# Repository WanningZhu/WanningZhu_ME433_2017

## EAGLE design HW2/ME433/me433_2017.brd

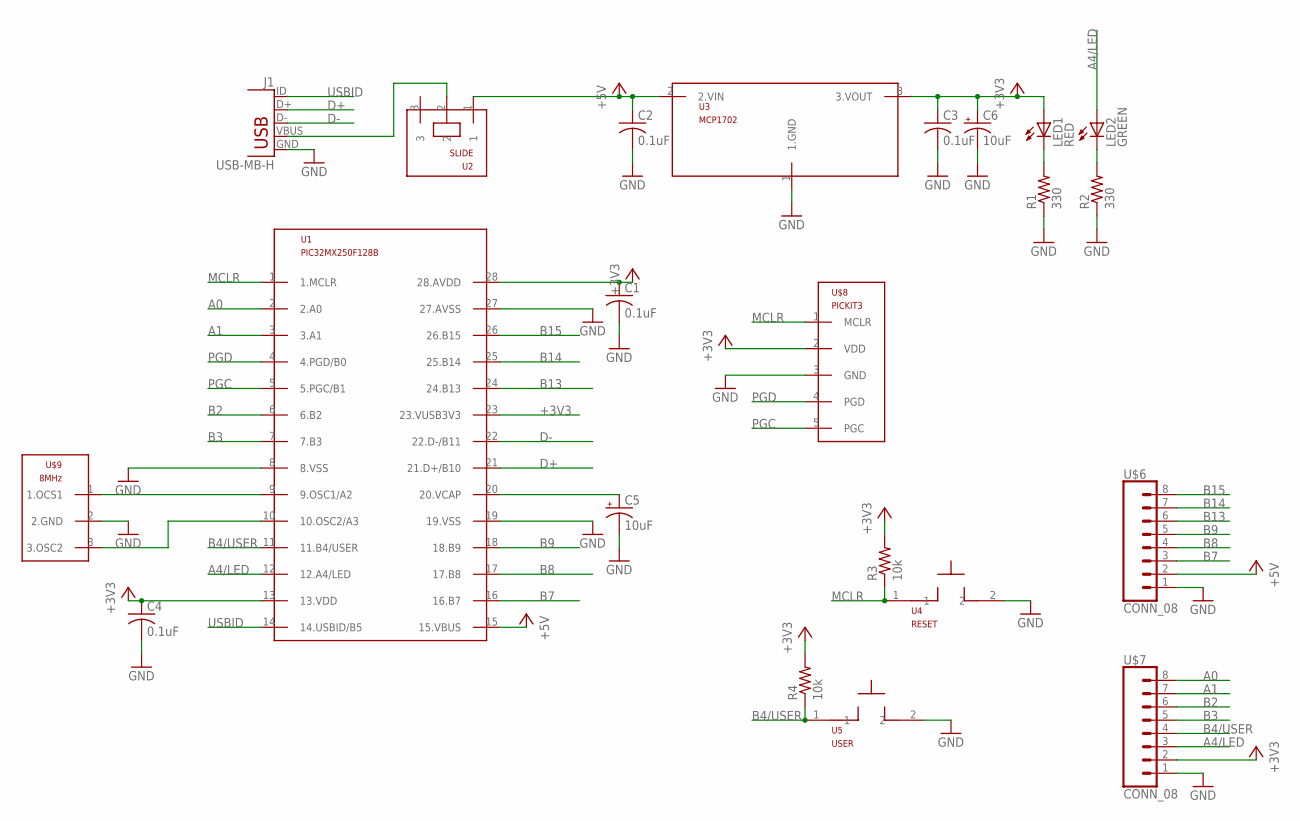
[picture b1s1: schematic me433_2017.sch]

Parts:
C1, C2, C3, C4: 0.1uF; C025-025X050
C5, C6: 10uF; B45181B
J1: USB-MB-H
LED1: RED; LED3MM
LED2: GREEN; LED3MM
R1, R2: 330; 0207/10
R3, R4: 10k; 0207/10
U1: PIC32MX250F128B; DIL28-3
U2: SLIDE
U3: MCP1702; TO92
U4: RESET; PB
U5: USER; PB
U$6, U$7: CONN_08; 1X08
U$8: PICKIT3; 1X05
U$9: 8MHz; OSC

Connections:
+3V3: C1.1, C3.1, C4.1, C6.+, LED1.A, R3.2, R4.2, U1.13 (13.VDD), U1.23 (23.VUSB3V3), U1.28 (28.AVDD), U3.3 (3.VOUT), U$7.2, U$8.2 (VDD)
+5V: C2.1, U1.15 (15.VBUS), U2.1, U3.2 (2.VIN), U$6.2
A0: U1.2 (2.A0), U$7.8
A1: U1.3 (3.A1), U$7.7
A4/LED: LED2.A, U1.12 (12.A4/LED), U$7.3
B2: U1.6 (6.B2), U$7.6
B3: U1.7 (7.B3), U$7.5
B4/USER: R4.1, U1.11 (11.B4/USER), U5.1, U$7.4
B7: U1.16 (16.B7), U$6.3
B8: U1.17 (17.B8), U$6.4
B9: U1.18 (18.B9), U$6.5
B13: U1.24 (24.B13), U$6.6
B14: U1.25 (25.B14), U$6.7
B15: U1.26 (26.B15), U$6.8
D+: J1.D+, U1.21 (21.D+/B10)
D-: J1.D-, U1.22 (22.D-/B11)
GND: C1.2, C2.2, C3.2, C4.2, C5.-, C6.-, J1.GND, R1.1, R2.1, U1.8 (8.VSS), U1.19 (19.VSS), U1.27 (27.AVSS), U3.1 (1.GND), U4.2, U5.2, U$6.1, U$7.1, U$8.3 (GND), U$9.2 (2.GND)
MCLR: R3.1, U1.1 (1.MCLR), U4.1, U$8.1 (MCLR)
unnamed: J1.VBUS, U2.2
unnamed: U1.9 (9.OSC1/A2), U$9.1 (1.OCS1)
unnamed: LED1.K (C), R1.2
unnamed: LED2.K (C), R2.2
unnamed: U1.10 (10.OSC2/A3), U$9.3 (3.OSC2)
unnamed: C5.+, U1.20 (20.VCAP)
PGC: U1.5 (5.PGC/B1), U$8.5 (PGC)
PGD: U1.4 (4.PGD/B0), U$8.4 (PGD)
USBID: J1.ID, U1.14 (14.USBID/B5)

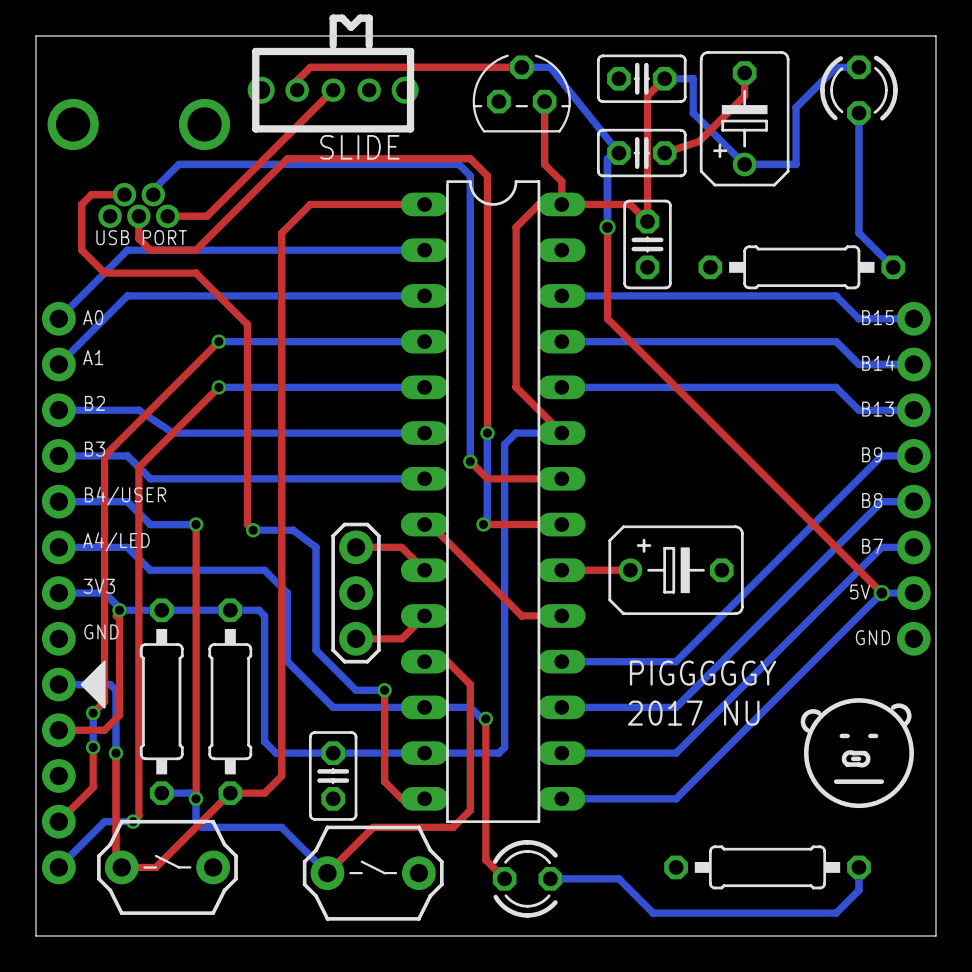
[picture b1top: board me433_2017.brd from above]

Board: 2 copper layers, 50.0 x 50.0 mm, 22 parts (0 on the bottom side), 27 nets.

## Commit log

2017-05-22 reset up GitHub
2017-05-23 some change
2017-05-23 test change
2017-05-23 add client
2017-05-24 start HW11
2017-05-24 finish HW11
2017-05-24 improvement
2017-05-25 finish HW12
2017-05-26 finish HW13
2017-05-26 finish HW14
2017-06-05 finish HW19
2017-06-08 Final project first commit
2017-06-08 finish Final project
2017-06-09 upload HW15
2017-06-09 upload HW16
2017-06-09 upload HW17
